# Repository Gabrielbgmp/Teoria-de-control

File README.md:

# Teoría de Control - Péndulo Invertido

Este repositorio contiene el código, la biblioteca personalizada, los recursos y el diseño de la PCB relacionados con el proyecto de un **péndulo invertido** controlado mediante un microcontrolador ESP32. Desarrollado como parte de la Prácticas 4 y 6 del curso de Teoría de Control, el proyecto incluye la implementación de controladores PID y un modelo 3D del péndulo, junto con el diseño de la placa de circuito impreso.

## Descripción del Proyecto

El péndulo invertido es un sistema clásico de control automático donde un péndulo montado sobre un carro móvil debe mantenerse en posición vertical usando un motor. Este repositorio alberga:

- **Biblioteca `PIDController`**: Implementación en C++ de tres controladores PID (básico, IIR y con filtro pasa baja) adaptada para ESP32.
- **Ejemplo de Control**: Código para controlar el péndulo en modos de balanceo puro y balanceo con posición.
- **Modelo 3D**: Archivo STL para replicar el diseño físico del péndulo.
- **Diseño PCB**: Esquema y diseño de la placa de circuito impreso que integra los componentes necesarios para el sistema.
- **Documentación**: Instrucciones y detalles del proyecto.

## Contenido del Repositorio

- **`PIDController/`**: Carpeta con los archivos `PIDController.h` y `PID.cpp` de la biblioteca.
- **`examples/PendulumControl/`**: Ejemplo de uso para el ESP32 (archivo `.ino`).
- **`pendulum.stl`**: Modelo 3D del péndulo invertido.
- **`pcb/`**: Carpeta con los archivos del diseño de la PCB .
- **`README.md`**: Este archivo con información general.

## Características

- **Controladores PID**: 
  - Básico: Implementación estándar en tiempo discreto.
  - IIR: Con respuesta infinita por impulso.
  - Con filtro pasa baja: Para reducir ruido en el término derivativo.
- **Modos de Operación**: Balanceo del ángulo y control combinado de ángulo y posición.
- **Interfaz Serial**: Ajuste en tiempo real de ganancias PID y setpoints.
- **Frecuencia**: 100 Hz.
- **PCB**: Diseño personalizado para integrar el ESP32 y demas componentes.

## Requisitos

### Hardware
- ESP32.
- Impresión 3D.
- Componentes para ensamblar la PCB diseñada.

### Software
- Arduino IDE (configurado para ESP32).
- Biblioteca `PIDController` (incluida).
- Software de diseño PCB para visualizar o modificar el diseño.

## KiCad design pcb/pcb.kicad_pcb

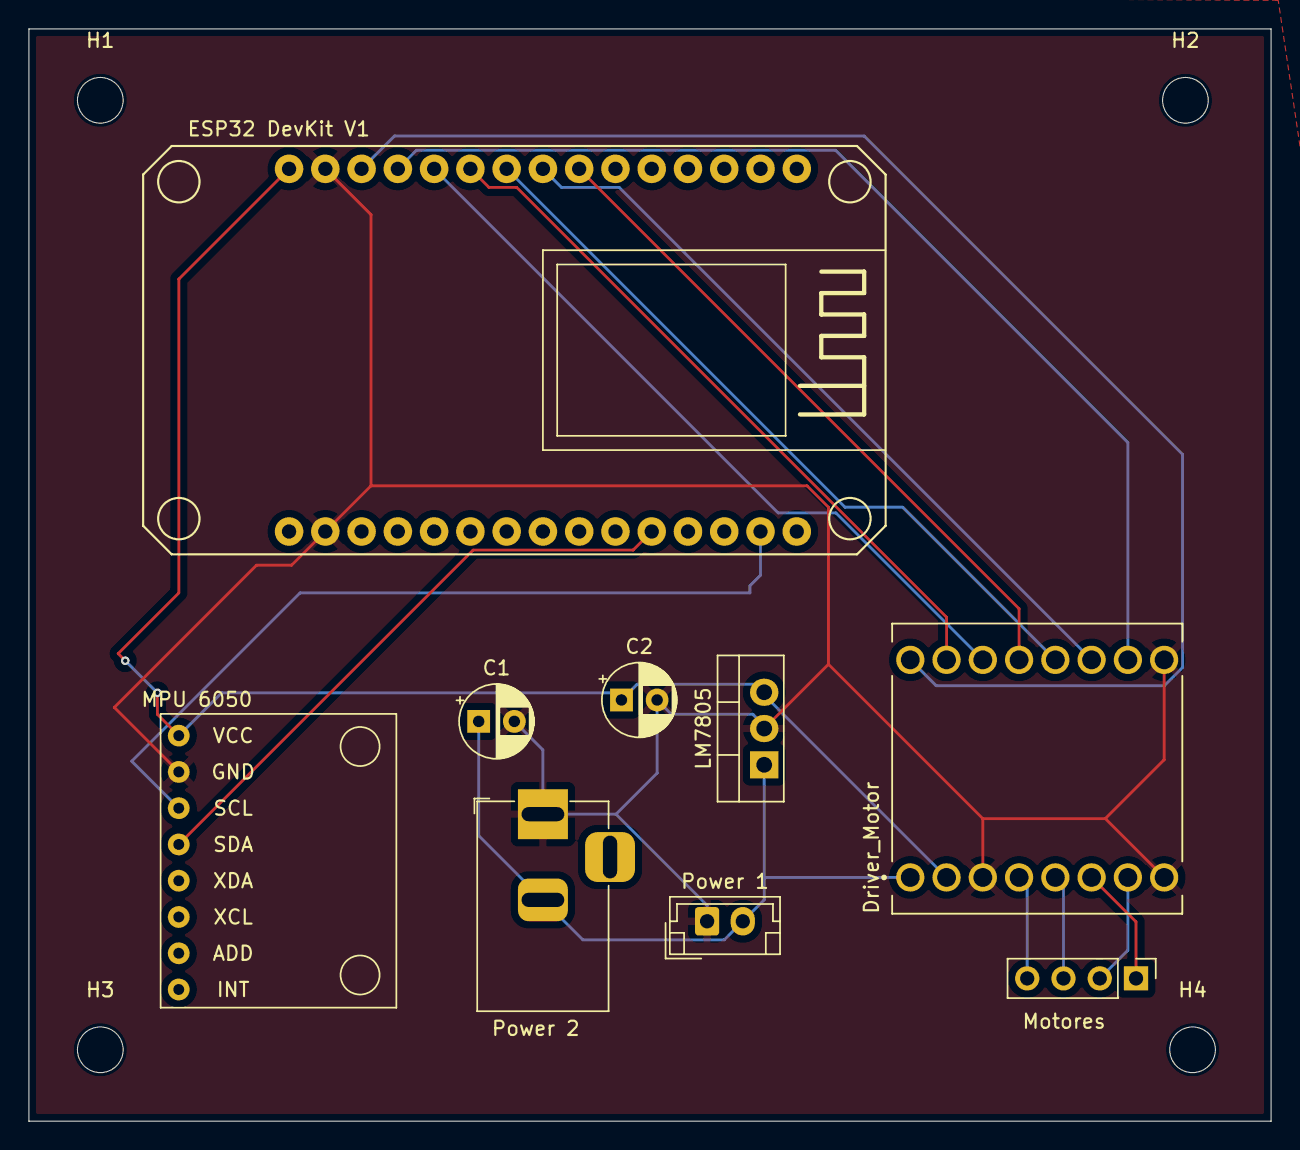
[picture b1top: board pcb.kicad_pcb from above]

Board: 2 copper layers, 87.0 x 76.5 mm, 13 parts (0 on the bottom side), 16 nets.

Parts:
C1, C2: C_Polarized; CP_Radial_D5.0mm_P2.50mm
Driver_Motor: ROB-14450; MODULE_ROB-14450
ESP32 DevKit V1: ESP32DevKitv1
H1, H2, H3, H4: MountingHole; MountingHole_3.2mm_M3
LM7805: LM7805_TO220; TO-220-3_Vertical
MPU 6050: module_mpu6050
Motores: Conn_01x04_Pin; PinHeader_1x04_P2.54mm_Vertical
Power 1: Conn_01x02_Pin; JST_EH_B2B-EH-A_1x02_P2.50mm_Vertical
Power 2: Barrel_Jack_Switch; BarrelJack_Horizontal

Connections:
GND: C1.2, C2.2, Driver_Motor.3 (GND), Driver_Motor.8 (GND), Driver_Motor.9 (GND), ESP32 DevKit V1.2 (GND), ESP32 DevKit V1.29 (GND), LM7805.2 (GND), MPU 6050.2 (GND), Power 1.1, Power 2.1
unnamed: C1.1, Driver_Motor.1 (VM), LM7805.1 (VI), Power 1.2, Power 2.2
unnamed: Driver_Motor.6 (B02), Motores.1
unnamed: Driver_Motor.7 (B01), Motores.2
unnamed: Driver_Motor.5 (A02), Motores.3
unnamed: Driver_Motor.4 (A01), Motores.4
unnamed: Driver_Motor.10 (PWMB), ESP32 DevKit V1.27 (D12)
unnamed: Driver_Motor.16 (PWMA), ESP32 DevKit V1.28 (D13)
unnamed: Driver_Motor.14 (AI1), ESP32 DevKit V1.26 (D14)
unnamed: ESP32 DevKit V1.11 (D21), MPU 6050.4 (SDA)
unnamed: ESP32 DevKit V1.14 (D22), MPU 6050.3 (SCL)
unnamed: Driver_Motor.11 (BI2), ESP32 DevKit V1.23 (D25)
unnamed: Driver_Motor.12 (BI1), ESP32 DevKit V1.24 (D26)
unnamed: Driver_Motor.15 (AI2), ESP32 DevKit V1.25 (D27)
unnamed: Driver_Motor.13 (STBY), ESP32 DevKit V1.22 (D33)
unnamed: C2.1, Driver_Motor.2 (VCC), ESP32 DevKit V1.30 (VIN), LM7805.3 (VO), MPU 6050.1 (VCC)

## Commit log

2025-06-30 README.me
